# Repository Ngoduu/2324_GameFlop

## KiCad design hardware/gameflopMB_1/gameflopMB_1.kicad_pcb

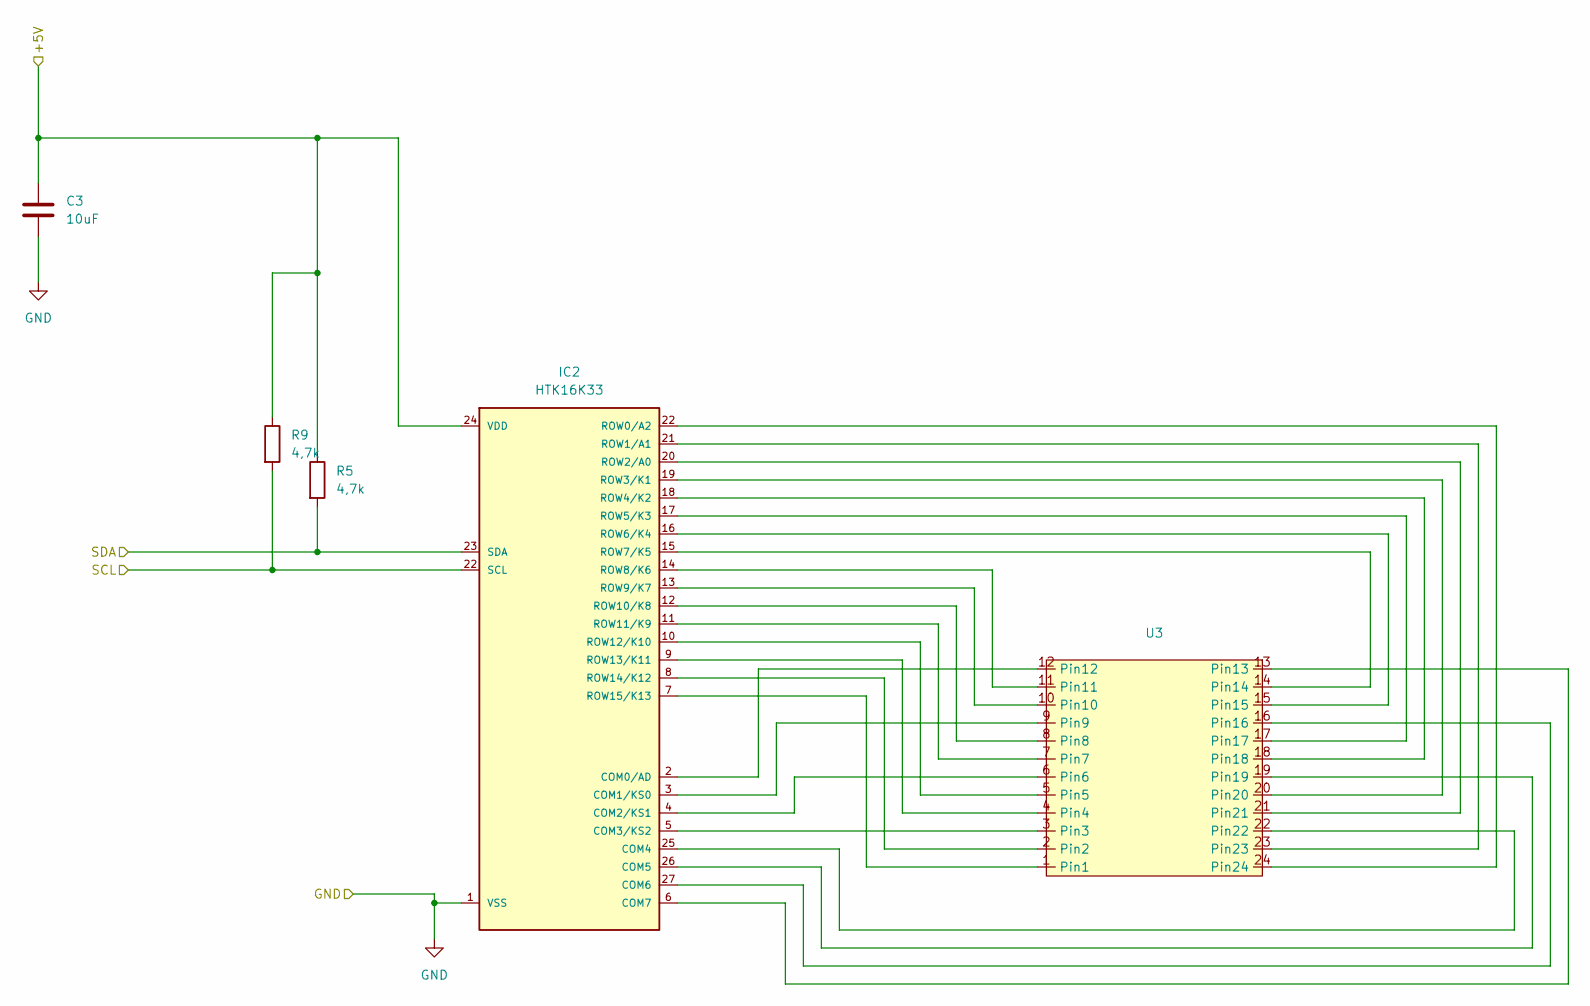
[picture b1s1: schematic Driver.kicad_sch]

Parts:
C3: 10uF; C_0603_1608Metric_Pad1.08x0.95mm_HandSolder
IC2: HTK16K33; HT16K33
R5, R9: 4,7k; R_0805_2012Metric_Pad1.20x1.40mm_HandSolder
U3: BL-M12X883

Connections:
/Alim/+5V: C3.1, IC2.24 (VDD), R5.1, R9.1; also elsewhere on the board
/Driver0/SDA: IC2.23 (SDA), R5.2; also elsewhere on the board
GND: C3.2, IC2.1 (VSS); also elsewhere on the board
unnamed: IC2.2 (COM0/AD), U3.12 (Pin12)
unnamed: IC2.3 (COM1/KS0), U3.9 (Pin9)
unnamed: IC2.4 (COM2/KS1), U3.6 (Pin6)
unnamed: IC2.5 (COM3/KS2), U3.3 (Pin3)
unnamed: IC2.25 (COM4), U3.22 (Pin22)
unnamed: IC2.26 (COM5), U3.19 (Pin19)
unnamed: IC2.27 (COM6), U3.16 (Pin16)
unnamed: IC2.6 (COM7), U3.13 (Pin13)
unnamed: IC2.21 (ROW1/A1), U3.23 (Pin23)
unnamed: IC2.20 (ROW2/A0), U3.21 (Pin21)
unnamed: IC2.19 (ROW3/K1), U3.20 (Pin20)
unnamed: IC2.18 (ROW4/K2), U3.18 (Pin18)
unnamed: IC2.17 (ROW5/K3), U3.17 (Pin17)
unnamed: IC2.16 (ROW6/K4), U3.15 (Pin15)
unnamed: IC2.15 (ROW7/K5), U3.14 (Pin14)
unnamed: IC2.14 (ROW8/K6), U3.11 (Pin11)
unnamed: IC2.13 (ROW9/K7), U3.10 (Pin10)
unnamed: IC2.12 (ROW10/K8), U3.8 (Pin8)
unnamed: IC2.11 (ROW11/K9), U3.7 (Pin7)
unnamed: IC2.10 (ROW12/K10), U3.5 (Pin5)
unnamed: IC2.9 (ROW13/K11), U3.4 (Pin4)
unnamed: IC2.8 (ROW14/K12), U3.2 (Pin2)
unnamed: IC2.7 (ROW15/K13), U3.1 (Pin1)

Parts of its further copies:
C4, C5, C11: 10uF; C_0603_1608Metric_Pad1.08x0.95mm_HandSolder
IC6, IC7, IC8: HTK16K33; HT16K33
R6, R7, R8, R10, R11, R12: 4,7k; R_0805_2012Metric_Pad1.20x1.40mm_HandSolder
U4, U7, U8: BL-M12X883

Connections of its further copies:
/Alim/+5V: C4.1, C5.1, C11.1, IC6.24 (VDD), IC7.24 (VDD), IC8.24 (VDD), R6.1, R7.1, R8.1, R10.1, R11.1, R12.1; also elsewhere on the board
/Driver0/SDA: IC6.23 (SDA), IC7.23 (SDA), IC8.23 (SDA), R6.2, R7.2, R8.2; also elsewhere on the board
GND: C4.2, C5.2, C11.2, IC6.1 (VSS), IC7.1 (VSS), IC8.1 (VSS); also elsewhere on the board
unnamed: IC6.2 (COM0/AD), U4.12 (Pin12)
unnamed: IC6.3 (COM1/KS0), U4.9 (Pin9)
unnamed: IC6.4 (COM2/KS1), U4.6 (Pin6)
unnamed: IC6.5 (COM3/KS2), U4.3 (Pin3)
unnamed: IC6.25 (COM4), U4.22 (Pin22)
unnamed: IC6.26 (COM5), U4.19 (Pin19)
unnamed: IC6.27 (COM6), U4.16 (Pin16)
unnamed: IC6.6 (COM7), U4.13 (Pin13)
unnamed: IC6.22 (SCL), U4.24 (Pin24)
unnamed: IC6.21 (ROW1/A1), U4.23 (Pin23)
unnamed: IC6.20 (ROW2/A0), U4.21 (Pin21)
unnamed: IC6.19 (ROW3/K1), U4.20 (Pin20)
unnamed: IC6.18 (ROW4/K2), U4.18 (Pin18)
unnamed: IC6.17 (ROW5/K3), U4.17 (Pin17)
unnamed: IC6.16 (ROW6/K4), U4.15 (Pin15)
unnamed: IC6.15 (ROW7/K5), U4.14 (Pin14)
unnamed: IC6.14 (ROW8/K6), U4.11 (Pin11)
unnamed: IC6.13 (ROW9/K7), U4.10 (Pin10)
unnamed: IC6.12 (ROW10/K8), U4.8 (Pin8)
unnamed: IC6.11 (ROW11/K9), U4.7 (Pin7)
unnamed: IC6.10 (ROW12/K10), U4.5 (Pin5)
unnamed: IC6.9 (ROW13/K11), U4.4 (Pin4)
unnamed: IC6.8 (ROW14/K12), U4.2 (Pin2)
unnamed: IC6.7 (ROW15/K13), U4.1 (Pin1)
unnamed: IC7.2 (COM0/AD), U7.12 (Pin12)
unnamed: IC7.3 (COM1/KS0), U7.9 (Pin9)
unnamed: IC7.4 (COM2/KS1), U7.6 (Pin6)
unnamed: IC7.5 (COM3/KS2), U7.3 (Pin3)
unnamed: IC7.25 (COM4), U7.22 (Pin22)
unnamed: IC7.26 (COM5), U7.19 (Pin19)
unnamed: IC7.27 (COM6), U7.16 (Pin16)
unnamed: IC7.6 (COM7), U7.13 (Pin13)
unnamed: IC7.21 (ROW1/A1), U7.23 (Pin23)
unnamed: IC7.20 (ROW2/A0), U7.21 (Pin21)
unnamed: IC7.19 (ROW3/K1), U7.20 (Pin20)
unnamed: IC7.18 (ROW4/K2), U7.18 (Pin18)
unnamed: IC7.17 (ROW5/K3), U7.17 (Pin17)
unnamed: IC7.16 (ROW6/K4), U7.15 (Pin15)
unnamed: IC7.15 (ROW7/K5), U7.14 (Pin14)
unnamed: IC7.14 (ROW8/K6), U7.11 (Pin11)
unnamed: IC7.13 (ROW9/K7), U7.10 (Pin10)
unnamed: IC7.12 (ROW10/K8), U7.8 (Pin8)
unnamed: IC7.11 (ROW11/K9), U7.7 (Pin7)
unnamed: IC7.10 (ROW12/K10), U7.5 (Pin5)
unnamed: IC7.9 (ROW13/K11), U7.4 (Pin4)
unnamed: IC7.8 (ROW14/K12), U7.2 (Pin2)
unnamed: IC7.7 (ROW15/K13), U7.1 (Pin1)
unnamed: IC8.2 (COM0/AD), U8.12 (Pin12)
unnamed: IC8.3 (COM1/KS0), U8.9 (Pin9)
unnamed: IC8.4 (COM2/KS1), U8.6 (Pin6)
unnamed: IC8.5 (COM3/KS2), U8.3 (Pin3)
unnamed: IC8.25 (COM4), U8.22 (Pin22)
unnamed: IC8.26 (COM5), U8.19 (Pin19)
unnamed: IC8.27 (COM6), U8.16 (Pin16)
unnamed: IC8.6 (COM7), U8.13 (Pin13)
unnamed: IC8.22 (SCL), U8.24 (Pin24)
unnamed: IC8.21 (ROW1/A1), U8.23 (Pin23)
unnamed: IC8.20 (ROW2/A0), U8.21 (Pin21)
unnamed: IC8.19 (ROW3/K1), U8.20 (Pin20)
unnamed: IC8.18 (ROW4/K2), U8.18 (Pin18)
unnamed: IC8.17 (ROW5/K3), U8.17 (Pin17)
unnamed: IC8.16 (ROW6/K4), U8.15 (Pin15)
unnamed: IC8.15 (ROW7/K5), U8.14 (Pin14)
unnamed: IC8.14 (ROW8/K6), U8.11 (Pin11)
unnamed: IC8.13 (ROW9/K7), U8.10 (Pin10)
unnamed: IC8.12 (ROW10/K8), U8.8 (Pin8)
unnamed: IC8.11 (ROW11/K9), U8.7 (Pin7)
unnamed: IC8.10 (ROW12/K10), U8.5 (Pin5)
unnamed: IC8.9 (ROW13/K11), U8.4 (Pin4)
unnamed: IC8.8 (ROW14/K12), U8.2 (Pin2)
unnamed: IC8.7 (ROW15/K13), U8.1 (Pin1)

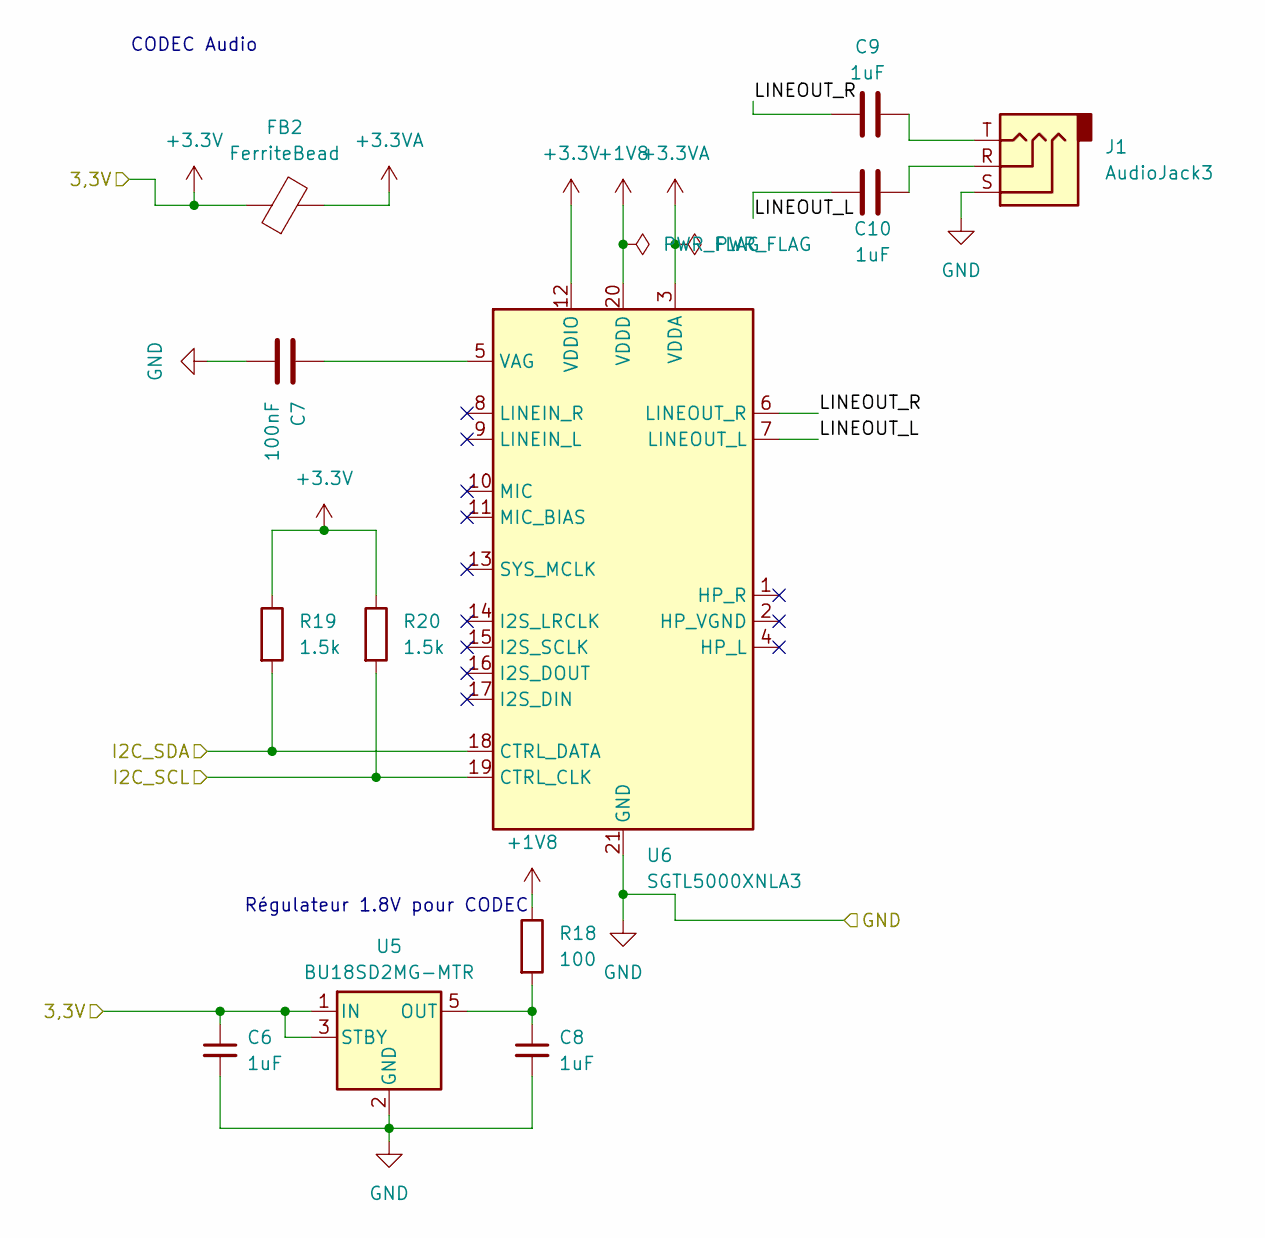
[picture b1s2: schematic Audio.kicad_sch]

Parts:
C6, C8: 1uF; C_0603_1608Metric_Pad1.08x0.95mm_HandSolder; LCSC Part C15849
C7: 100nF; C_0603_1608Metric_Pad1.08x0.95mm_HandSolder
C9, C10: 1uF; C_0603_1608Metric_Pad1.08x0.95mm_HandSolder
FB2: FerriteBead; L_0603_1608Metric
J1: AudioJack3; Jack_3.5mm_CUI_SJ-3523-SMT_Horizontal
R18: 100; R_0805_2012Metric_Pad1.20x1.40mm_HandSolder
R19, R20: 1.5k; R_0805_2012Metric_Pad1.20x1.40mm_HandSolder
U5: BU18SD2MG-MTR; SOT-23-5; LCSC Part C3750384
U6: SGTL5000XNLA3; QFN-20-1EP_3x3mm_P0.4mm_EP1.65x1.65mm

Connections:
+1V8: R18.1, U6.20 (VDDD)
+3.3V: C6.1, FB2.1, R19.1, R20.1, U5.1 (IN), U5.3 (STBY), U6.12 (VDDIO); also elsewhere on the board
+3.3VA: FB2.2, U6.3 (VDDA)
/Audio/I2C_SCL: R20.2, U6.19 (CTRL_CLK); also elsewhere on the board
/Audio/I2C_SDA: R19.2, U6.18 (CTRL_DATA); also elsewhere on the board
/Audio/LINEOUT_L: C10.1, U6.7 (LINEOUT_L)
/Audio/LINEOUT_R: C9.1, U6.6 (LINEOUT_R)
GND: C6.2, C7.2, C8.2, J1.S, U5.2 (GND), U6.21 (GND); also elsewhere on the board
unnamed: C9.2, J1.T
unnamed: C10.2, J1.R
unnamed: C8.1, R18.2, U5.5 (OUT)
unnamed: C7.1, U6.5 (VAG)

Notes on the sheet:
CODEC Audio
Régulateur 1.8V pour CODEC

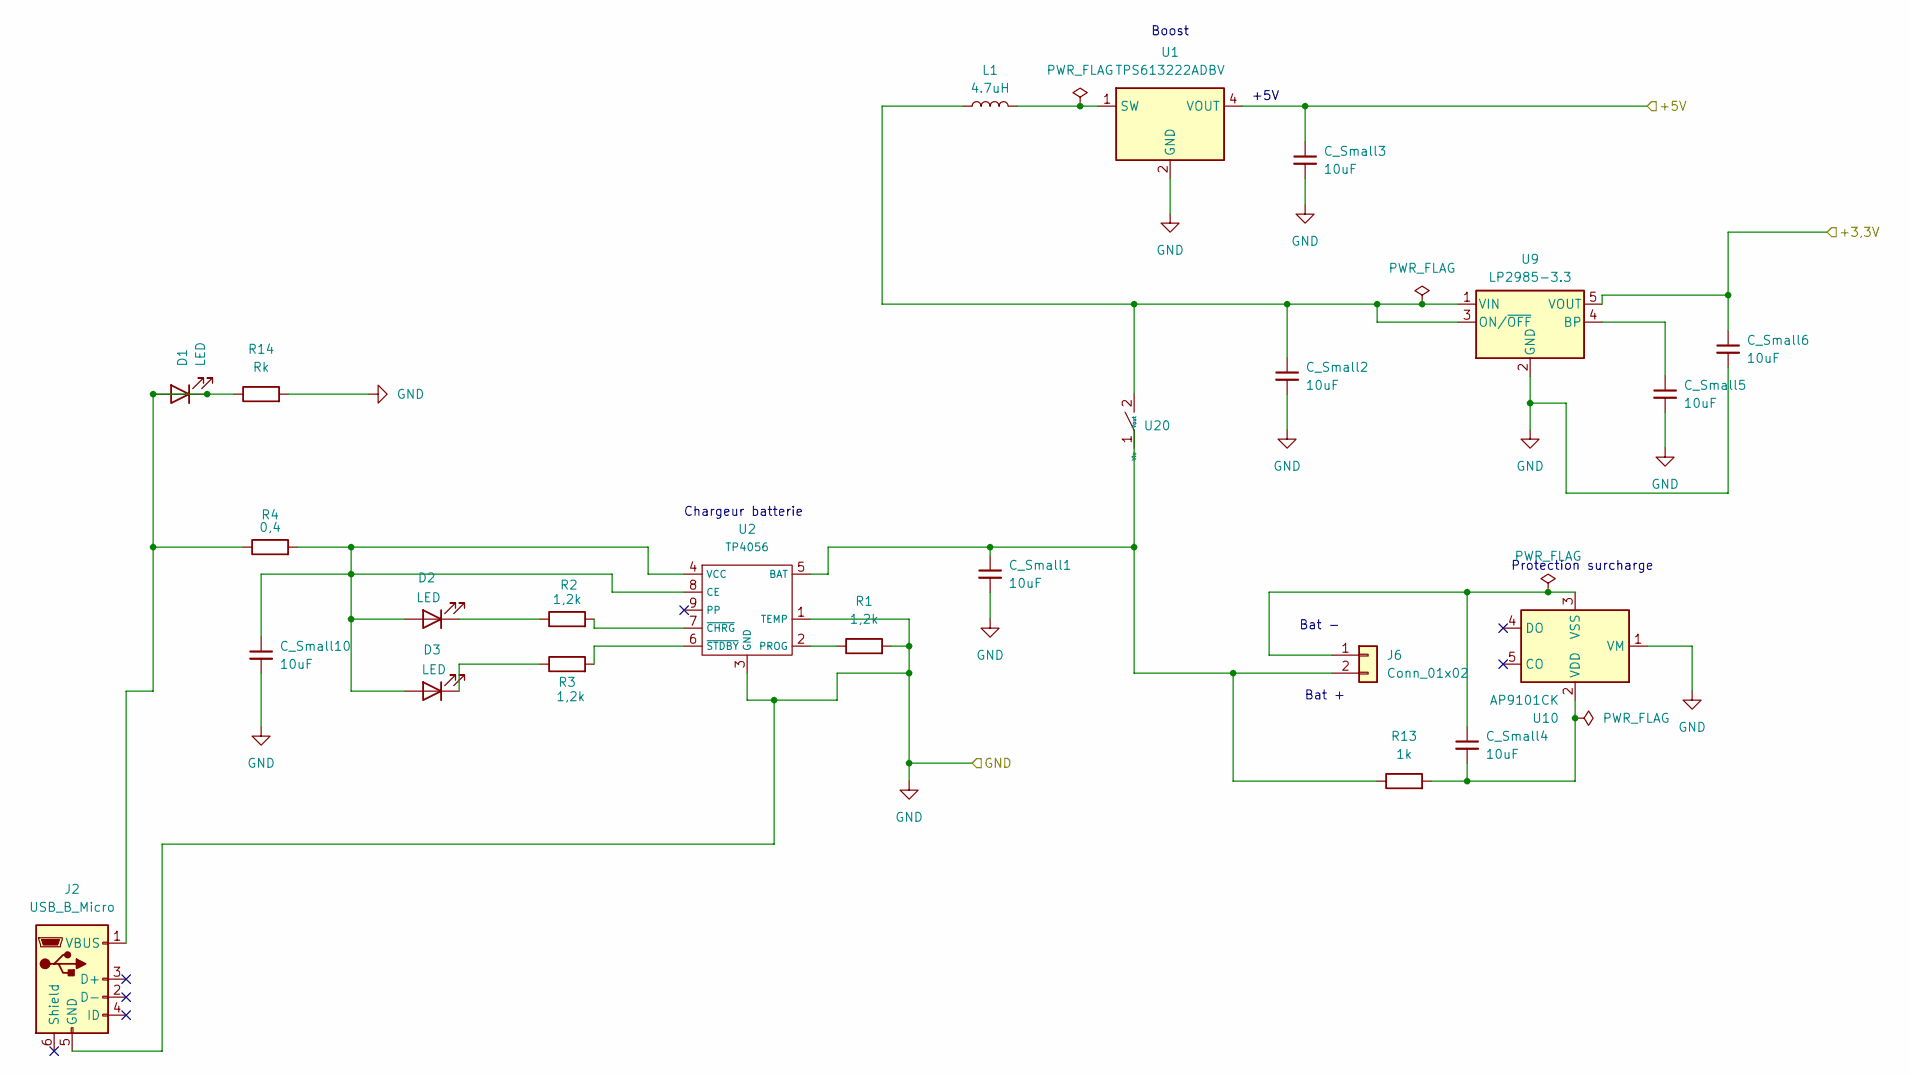
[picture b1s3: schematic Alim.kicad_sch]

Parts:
C_Small1, C_Small2, C_Small3, C_Small4, C_Small5, C_Small6, C_Small10: 10uF; C_0603_1608Metric_Pad1.08x0.95mm_HandSolder
D1, D2, D3: LED; LED_0603_1608Metric_Pad1.05x0.95mm_HandSolder
J2: USB_B_Micro; USB_Micro-B_Molex-105017-0001
J6: Conn_01x02; JST_XH_B2B-XH-A_1x02_P2.50mm_Vertical
L1: 4.7uH; L_0805_2012Metric_Pad1.05x1.20mm_HandSolder
R1, R2, R3: 1,2k; R_0805_2012Metric_Pad1.20x1.40mm_HandSolder
R4: 0,4; R_0805_2012Metric_Pad1.20x1.40mm_HandSolder
R13: 1k; R_0805_2012Metric_Pad1.20x1.40mm_HandSolder
R14: Rk; R_0805_2012Metric_Pad1.20x1.40mm_HandSolder
U1: TPS613222ADBV; SOT-23-5
U2: TP4056; SOIC-8-1EP_3.9x4.9mm_P1.27mm_EP2.29x3mm
U9: LP2985-3.3; SOT-23-5
U10: AP9101CK; SOT-23-5
U20: Switch rond

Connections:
+3.3V: C_Small6.1, U9.5 (VOUT); also elsewhere on the board
/Alim/+5V: C_Small3.1, U1.4 (VOUT); also elsewhere on the board
GND: C_Small1.2, C_Small2.2, C_Small3.2, C_Small5.2, C_Small6.2, C_Small10.2, J2.5 (GND), R1.2, R14.2, U1.2 (GND), U2.1 (TEMP), U2.3 (GND), U9.2 (GND), U10.1 (VM); also elsewhere on the board
unnamed: D1.1 (K), D1.2 (A), J2.1 (VBUS), R4.1, R14.1
unnamed: C_Small10.1, D2.2 (A), D3.2 (A), R4.2, U2.4 (VCC), U2.8 (CE)
unnamed: D2.1 (K), R2.1
unnamed: D3.1 (K), R3.1
unnamed: C_Small4.1, J6.1, U10.3 (VSS)
unnamed: C_Small1.1, J6.2, R13.1, U2.5 (BAT), U20.1 (Vin)
unnamed: L1.2, U1.1 (SW)
unnamed: R1.1, U2.2 (PROG)
unnamed: R2.2, U2.7 (~CHRG)
unnamed: R3.2, U2.6 (~STDBY)
unnamed: C_Small5.1, U9.4 (BP)
unnamed: C_Small4.2, R13.2, U10.2 (VDD)
unnamed: C_Small2.1, L1.1, U9.1 (VIN), U9.3 (ON/~OFF), U20.2 (Vout)

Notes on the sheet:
Protection surcharge
Boost
Chargeur batterie
Bat +
Bat -
+5V

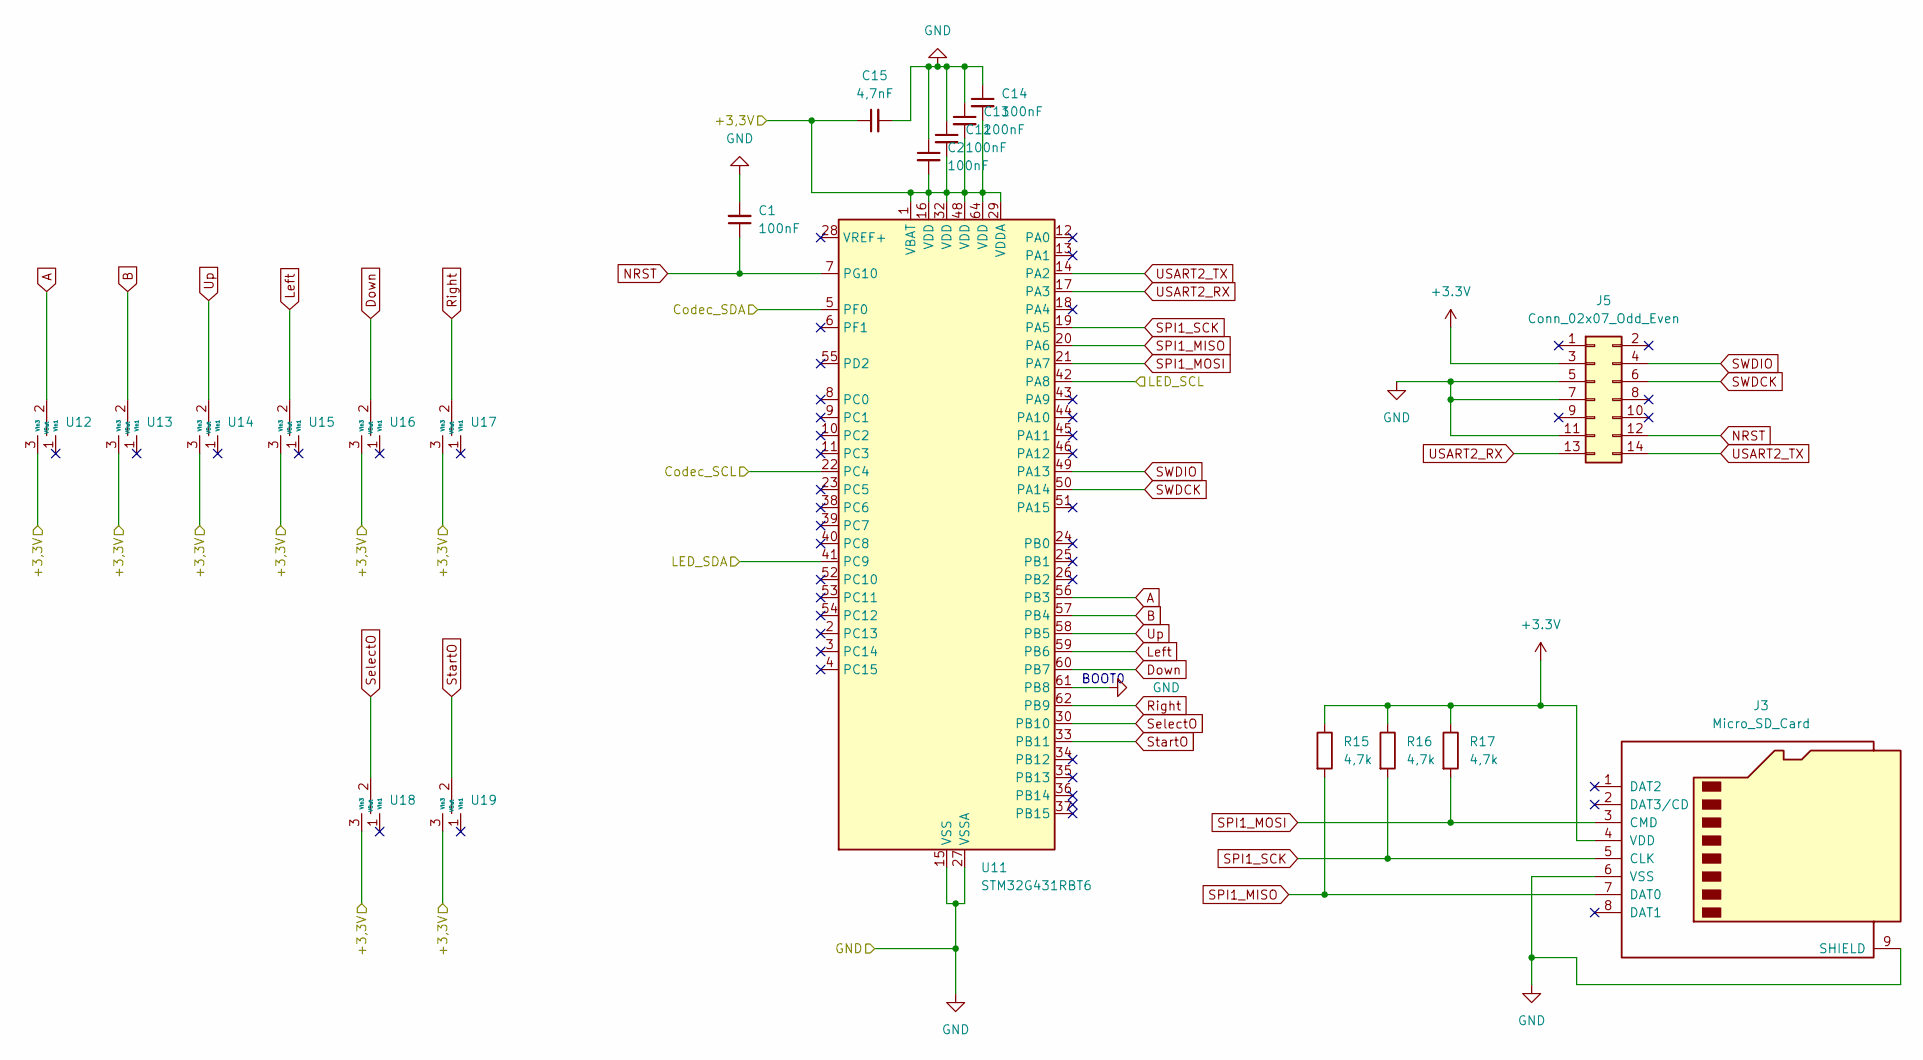
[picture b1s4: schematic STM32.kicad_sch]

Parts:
C1, C2, C12, C13, C14: 100nF; C_0603_1608Metric_Pad1.08x0.95mm_HandSolder
C15: 4,7nF; C_0603_1608Metric_Pad1.08x0.95mm_HandSolder
J3: Micro_SD_Card; microSD_HC_Molex_104031-0811
J5: Conn_02x07_Odd_Even; PinHeader_2x07_P1.27mm_Vertical
R15, R16, R17: 4,7k; R_0805_2012Metric_Pad1.20x1.40mm_HandSolder
U11: STM32G431RBT6; LQFP-64_10x10mm_P0.5mm
U12, U13, U14, U15, U16, U17, U18, U19: Switch carré

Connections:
+3.3V: C2.2, C12.2, C13.2, C14.2, C15.1, J3.4 (VDD), J5.3, R15.1, R16.1, R17.1, U11.1 (VBAT), U11.16 (VDD), U11.29 (VDDA), U11.32 (VDD), U11.48 (VDD), U11.64 (VDD), U12.3 (VIn3), U13.3 (VIn3), U14.3 (VIn3), U15.3 (VIn3), U16.3 (VIn3), U17.3 (VIn3), U18.3 (VIn3), U19.3 (VIn3); also elsewhere on the board
/Audio/I2C_SCL: U11.22 (PC4); also elsewhere on the board
/Audio/I2C_SDA: U11.5 (PF0); also elsewhere on the board
/Driver0/SDA: U11.41 (PC9); also elsewhere on the board
A: U11.56 (PB3), U12.2 (VOut)
B: U11.57 (PB4), U13.2 (VOut)
Down: U11.60 (PB7), U16.2 (VOut)
GND: C1.2, C2.1, C12.1, C13.1, C14.1, C15.2, J3.6 (VSS), J3.9 (SHIELD), J5.5, J5.7, J5.11, U11.15 (VSS), U11.27 (VSSA), U11.31 (VSS), U11.47 (VSS), U11.61 (PB8), U11.63 (VSS); also elsewhere on the board
Left: U11.59 (PB6), U15.2 (VOut)
NRST: C1.1, J5.12, U11.7 (PG10)
Right: U11.62 (PB9), U17.2 (VOut)
SPI1_MISO: J3.7 (DAT0), R15.2, U11.20 (PA6)
SPI1_MOSI: J3.3 (CMD), R17.2, U11.21 (PA7)
SPI1_SCK: J3.5 (CLK), R16.2, U11.19 (PA5)
SWDCK: J5.6, U11.50 (PA14)
SWDIO: J5.4, U11.49 (PA13)
SelectO: U11.30 (PB10), U18.2 (VOut)
StartO: U11.33 (PB11), U19.2 (VOut)
USART2_RX: J5.13, U11.17 (PA3)
USART2_TX: J5.14, U11.14 (PA2)
Up: U11.58 (PB5), U14.2 (VOut)

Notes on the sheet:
BOOT0

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
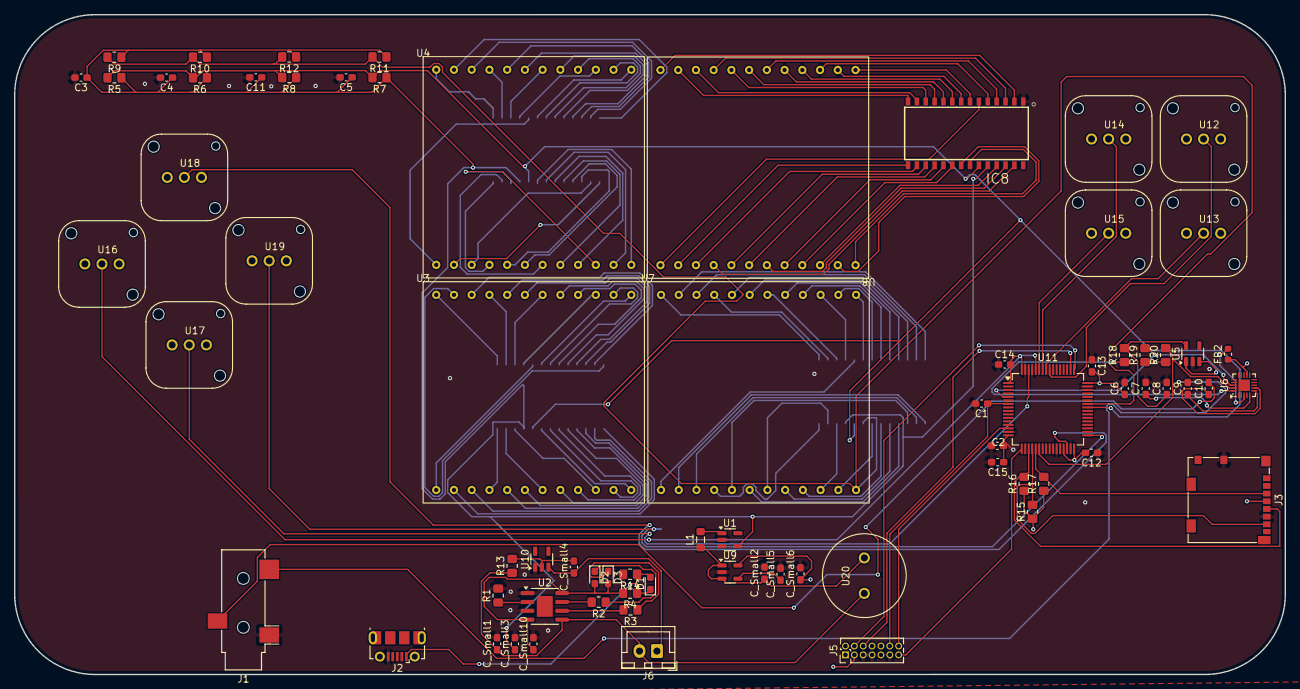
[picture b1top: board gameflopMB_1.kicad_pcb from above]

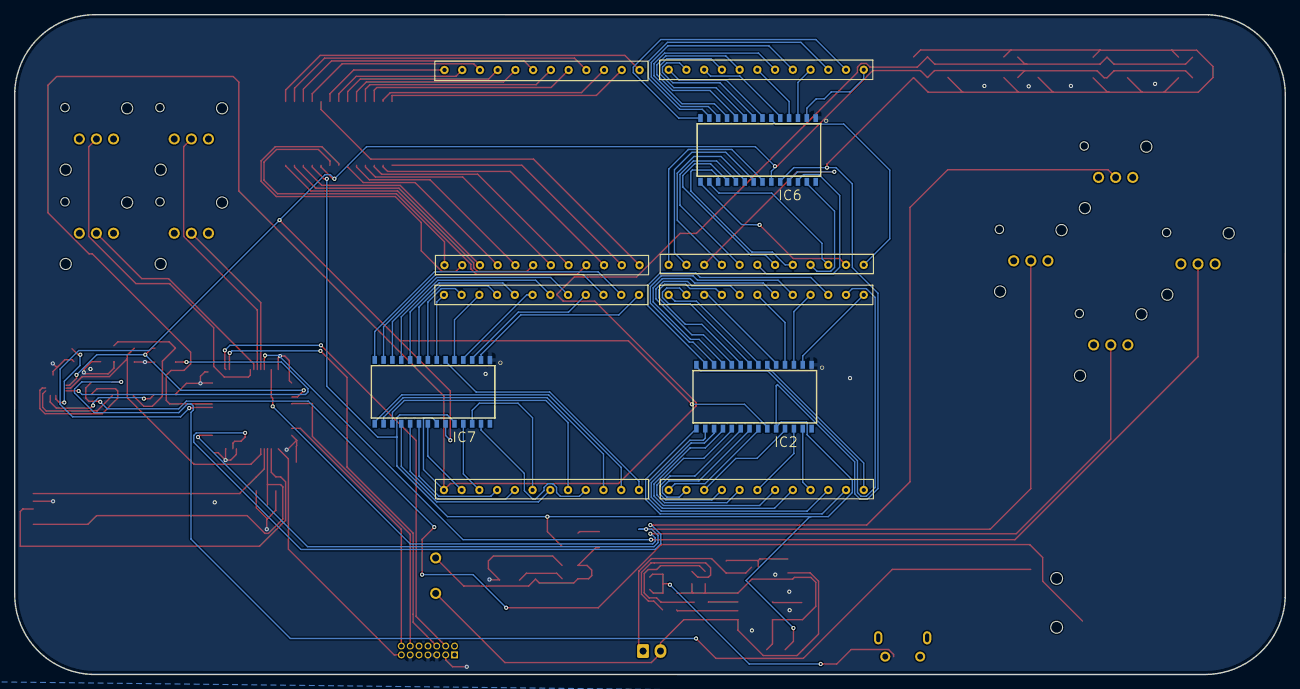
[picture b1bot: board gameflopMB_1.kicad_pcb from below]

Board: 4 copper layers, 182.0 x 94.5 mm, 76 parts (3 on the bottom side), 139 nets.

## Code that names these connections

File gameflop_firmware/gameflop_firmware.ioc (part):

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Mcu.Name=STM32G431R(6-8-B)Tx
Mcu.Package=LQFP64
Mcu.UserName=STM32G431RBTx
PA13.Mode=Serial_Wire
PA13.Signal=SYS_JTMS-SWDIO
PA14.Mode=Serial_Wire
PA14.Signal=SYS_JTCK-SWCLK
PA2.Mode=Asynchronous
PA2.Signal=USART2_TX
PA3.Mode=Asynchronous
PA3.Signal=USART2_RX
PA5.Mode=Full_Duplex_Master
PA5.Signal=SPI1_SCK
PA6.Mode=Full_Duplex_Master
PA6.Signal=SPI1_MISO
PA7.Mode=Full_Duplex_Master
PA7.Signal=SPI1_MOSI
PA8.Mode=I2C
PA8.Signal=I2C3_SCL
PB10.GPIOParameters=GPIO_Label
PB10.GPIO_Label=Select
PB10.Signal=GPXTI10
PB11.GPIOParameters=GPIO_Label
PB11.GPIO_Label=Start
PB11.Signal=GPXTI11
PB3.GPIOParameters=GPIO_Label
PB3.GPIO_Label=A
PB3.Signal=GPXTI3
PB4.GPIOParameters=GPIO_Label
PB4.GPIO_Label=B
PB4.Signal=GPXTI4
PB5.GPIOParameters=GPIO_Label
PB5.GPIO_Label=Up
PB5.Signal=GPXTI5
PB6.GPIOParameters=GPIO_Label
PB6.GPIO_Label=Left
PB6.Signal=GPXTI6
PB7.GPIOParameters=GPIO_Label
PB7.GPIO_Label=Down
PB7.Signal=GPXTI7
PB9.GPIOParameters=GPIO_Label
PB9.GPIO_Label=Right
PB9.Signal=GPXTI9
PC9.Mode=I2C
PC9.Signal=I2C3_SDA
RCC.HSE_VALUE=8000000
RCC.SYSCLKFreq_VALUE=16000000
board=custom

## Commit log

2024-04-24 new push
2024-05-15 Ajout du firmware
    Ajout du firmware
2024-05-31 last push hardware
